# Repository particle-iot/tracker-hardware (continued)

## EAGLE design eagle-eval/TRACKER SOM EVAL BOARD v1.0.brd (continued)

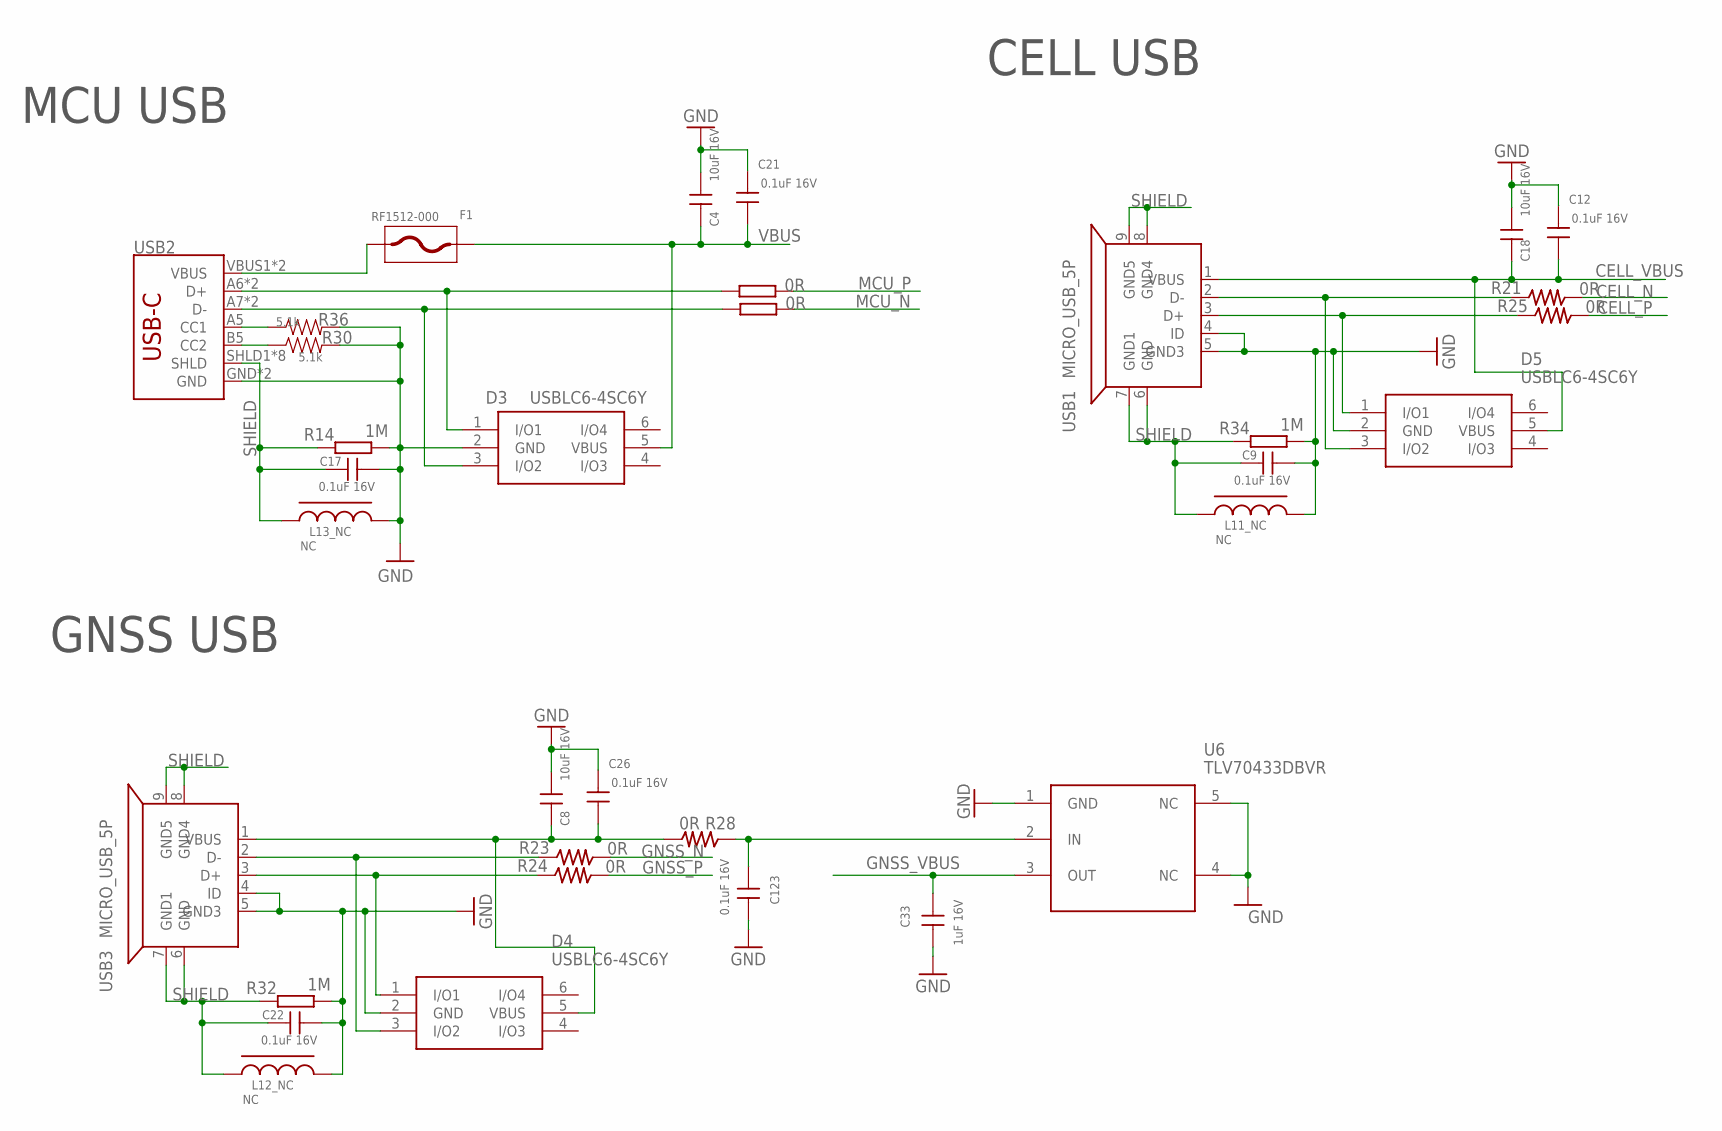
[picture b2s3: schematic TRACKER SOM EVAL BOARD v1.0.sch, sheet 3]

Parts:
C4, C8, C18: 10uF 16V; REDBEAR_C0603
C9, C17, C22: 0.1uF 16V; PARTICLE-SZ_C-0402
C12, C21, C26, C123: 0.1uF 16V; C-0402
C33: 1uF 16V; C0603
D3, D4, D5: USBLC6-4SC6Y; SOT95P280X145-6N
F1: RF1512-000; R1206
L11_NC, L12_NC, L13_NC: NC; R-0603A
R14, R32, R34: 1M; REDBEAR_R0603
R15, R16, R21, R23, R24, R25, R28: 0R; R-0402S
R30, R36: 5.1k; C0402
U6: TLV70433DBVR
USB1, USB3: MICRO_USB_5P; MICRO_USB
USB2: USB_C16PIN; USB-C-16P

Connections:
CELL_N: R21.2; also elsewhere on the board
CELL_P: R25.2; also elsewhere on the board
CELL_VBUS: C12.1, C18.2, D5.5 (VBUS), USB1.1 (VBUS); also elsewhere on the board
GND: C4.1, C8.1, C9.2, C12.2, C17.2, C18.1, C21.2, C22.2, C26.2, C33.2, C123.2, D3.2 (GND), D4.2 (GND), D5.2 (GND), L11_NC.2, L12_NC.2, L13_NC.2, R14.2, R30.2, R32.2, R34.2, R36.2, U6.1 (GND), U6.4 (NC), U6.5 (NC), USB1.4 (ID), USB1.5 (GND3), USB2.GND, USB2.GND2 (GND), USB3.4 (ID), USB3.5 (GND3); also elsewhere on the board
GNSS_N: R23.2; also elsewhere on the board
GNSS_P: R24.2; also elsewhere on the board
GNSS_VBUS: C33.1, U6.3 (OUT); also elsewhere on the board
MCU_N: R15.2; also elsewhere on the board
MCU_P: R16.2; also elsewhere on the board
unnamed: D3.3 (I/O2), R15.1, USB2.A7 (D-), USB2.B7 (D-)
unnamed: D3.1 (I/O1), R16.1, USB2.A6 (D+), USB2.B6 (D+)
unnamed: D4.3 (I/O2), R23.1, USB3.2 (D-)
unnamed: D5.3 (I/O2), R21.1, USB1.2 (D-)
unnamed: D5.1 (I/O1), R25.1, USB1.3 (D+)
unnamed: F1.1, USB2.VBUS1 (VBUS), USB2.VBUS2 (VBUS)
unnamed: D4.1 (I/O1), R24.1, USB3.3 (D+)
unnamed: C123.1, R28.1, U6.2 (IN)
unnamed: R30.1, USB2.B5 (CC2)
unnamed: R36.1, USB2.A5 (CC1)
SHIELD: C9.1, C17.1, C22.1, L11_NC.1, L12_NC.1, L13_NC.1, R14.1, R32.1, R34.1, USB1.6 (GND), USB1.7 (GND1), USB1.8 (GND4), USB1.9 (GND5), USB2.SHLD1 (SHLD), USB2.SHLD2 (SHLD), USB2.SHLD3 (SHLD), USB2.SHLD4 (SHLD), USB2.SHLD5 (SHLD), USB2.SHLD6 (SHLD), USB2.SHLD7 (SHLD), USB2.SHLD8 (SHLD), USB3.6 (GND), USB3.7 (GND1), USB3.8 (GND4), USB3.9 (GND5)
U_VBUS: C8.2, C26.1, D4.5 (VBUS), R28.2, USB3.1 (VBUS)
VBUS: C4.2, C21.1, D3.5 (VBUS), F1.2; also elsewhere on the board

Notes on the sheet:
MCU USB
CELL USB
GNSS USB

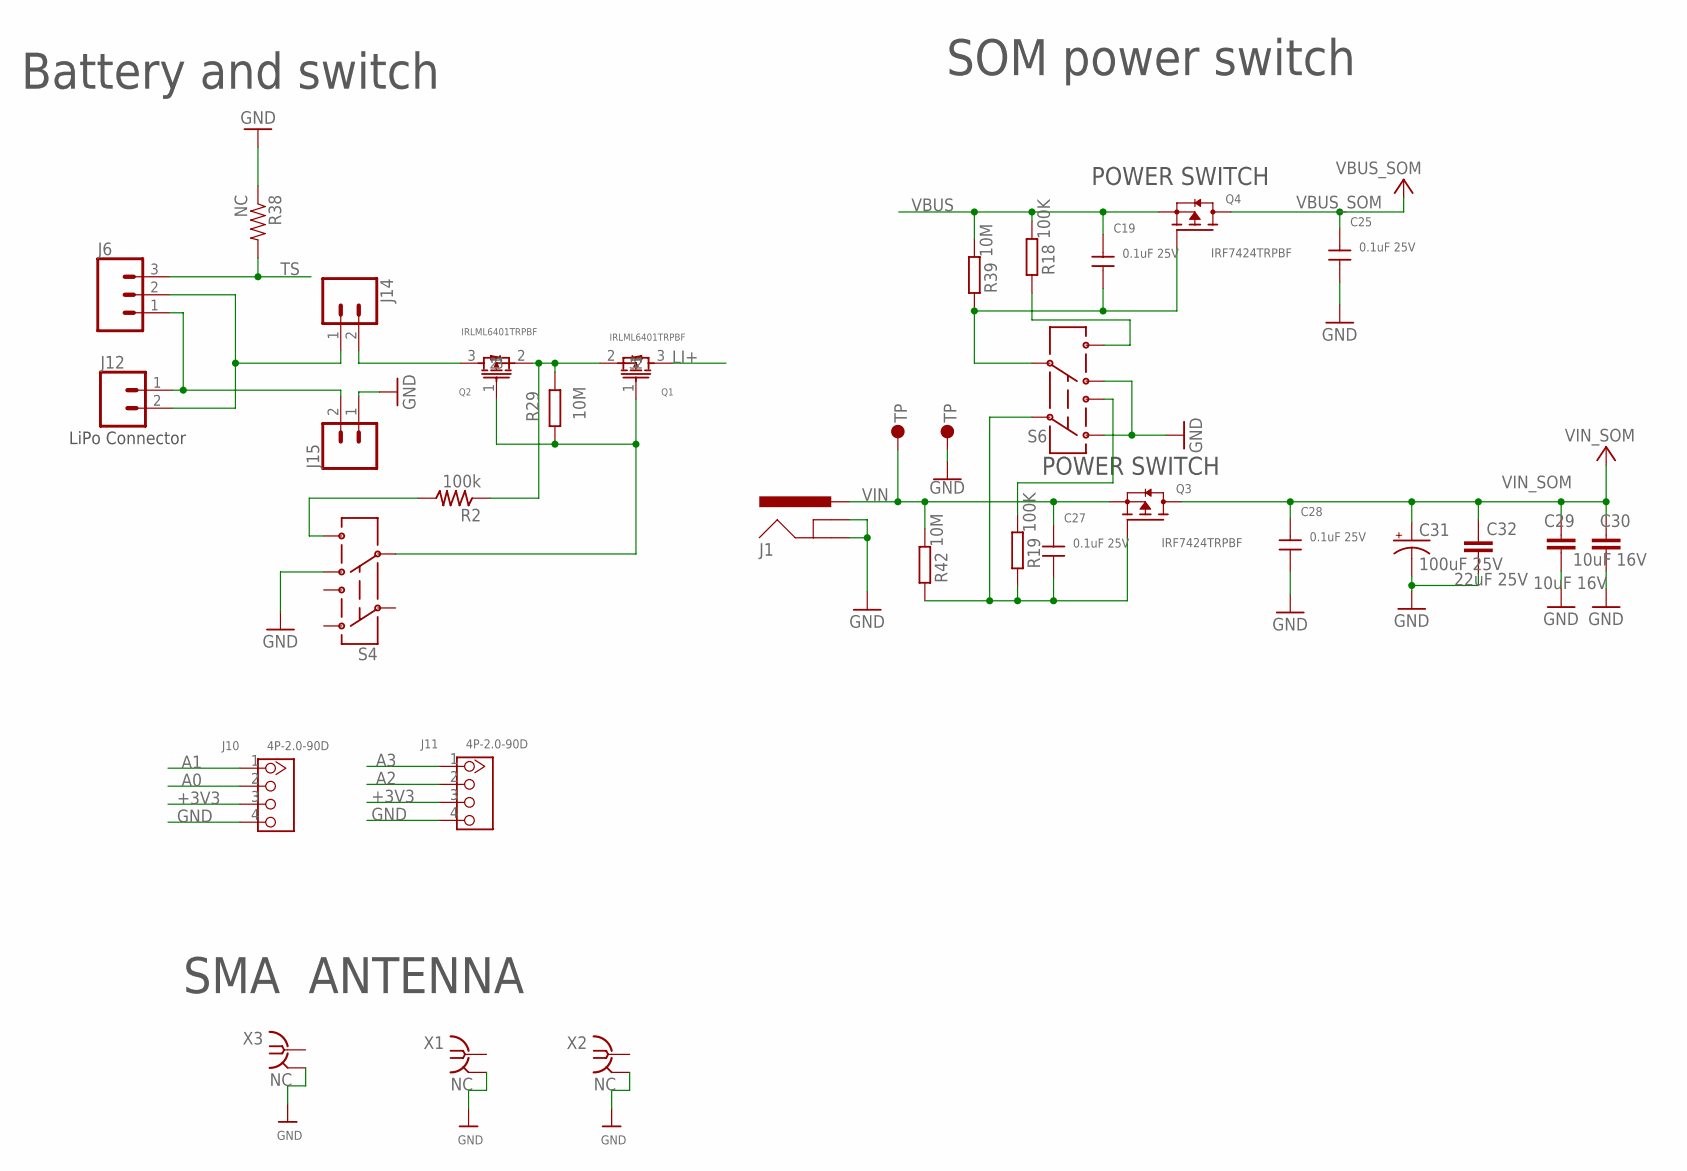
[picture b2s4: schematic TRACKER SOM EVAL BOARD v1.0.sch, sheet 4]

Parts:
C19, C25, C27, C28: 0.1uF 25V; C-0402
C29, C30: 10uF 16V; C0805
C31: 100uF 25V; PANASONIC_D
C32: 22uF 25V; C1206
J1: POWER_JACKSLT; POWER_JACK_SLOT
J6: CONN_03_2.54MM; 1X03
J10, J11: 4P-2.0-90D; HW4-2.0-90D
J12: CONN_02-JST-2MM-SMT; JST-2-SMD
J14, J15: CONN_02; 1X02
Q1, Q2: IRLML6401TRPBF; SOT-23
Q3, Q4: IRF7424TRPBF; PMOS_IRF7424
R2: 100k; R-0402S
R18, R19: 100K; R0603
R29, R39, R42: 10M; R0603
R38: NC; 0603-RES
S4, S6: SWITCH-DPDT; SWITCH-2.5X3.2-6
U$9, U$10: TP2; TP70_BOT
X1, X2, X3: NC; BU-SMA-G

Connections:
+3V3: J10.3, J11.3; also elsewhere on the board
A0: J10.2; also elsewhere on the board
A1: J10.1; also elsewhere on the board
A2: J11.2; also elsewhere on the board
A3: J11.1; also elsewhere on the board
GND: C25.1, C28.1, C29.2, C30.2, C31.-, C32.2, J1.GND@1 (GNDBREAK), J1.GND@2 (GND), J10.4, J11.4, J15.1, R38.1, S4.4, S6.1, S6.4, U$10.P$1, X1.2, X1.3 (2), X1.4 (2), X1.5 (2), X2.2, X2.3 (2), X2.4 (2), X2.5 (2), X3.2, X3.3 (2), X3.4 (2), X3.5 (2); also elsewhere on the board
LI+: Q1.3; also elsewhere on the board
unnamed: J14.2, Q2.3
unnamed: R2.2, S4.6
unnamed: J6.1, J12.1 (2), J15.2
unnamed: R18.1, S6.6
unnamed: R19.2, S6.3
unnamed: J6.2, J12.2 (1), J14.1
unnamed: Q1.2, Q2.2, R2.1, R29.2
unnamed: Q1.1, Q2.1, R29.1, S4.5
SYS_PWR_EN1: C19.1, Q4.4 (G), R39.1, S6.5
SYS_PWR_EN2: C27.1, Q3.4 (G), R19.1, R42.1, S6.2
TS: J6.3, R38.2; also elsewhere on the board
VBUS: C19.2, Q4.1 (S), Q4.2 (S), Q4.3 (S), R18.2, R39.2; also elsewhere on the board
VBUS_SOM: C25.2, Q4.5 (D), Q4.6 (D), Q4.7 (D), Q4.8 (D); also elsewhere on the board
VIN: C27.2, J1.PWR, Q3.1 (S), Q3.2 (S), Q3.3 (S), R42.2, U$9.P$1
VIN_SOM: C28.2, C29.1, C30.1, C31.+, C32.1, Q3.5 (D), Q3.6 (D), Q3.7 (D), Q3.8 (D); also elsewhere on the board

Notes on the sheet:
LiPo Connector
SMA ANTENNA
SOM power switch
Battery and switch
POWER SWITCH

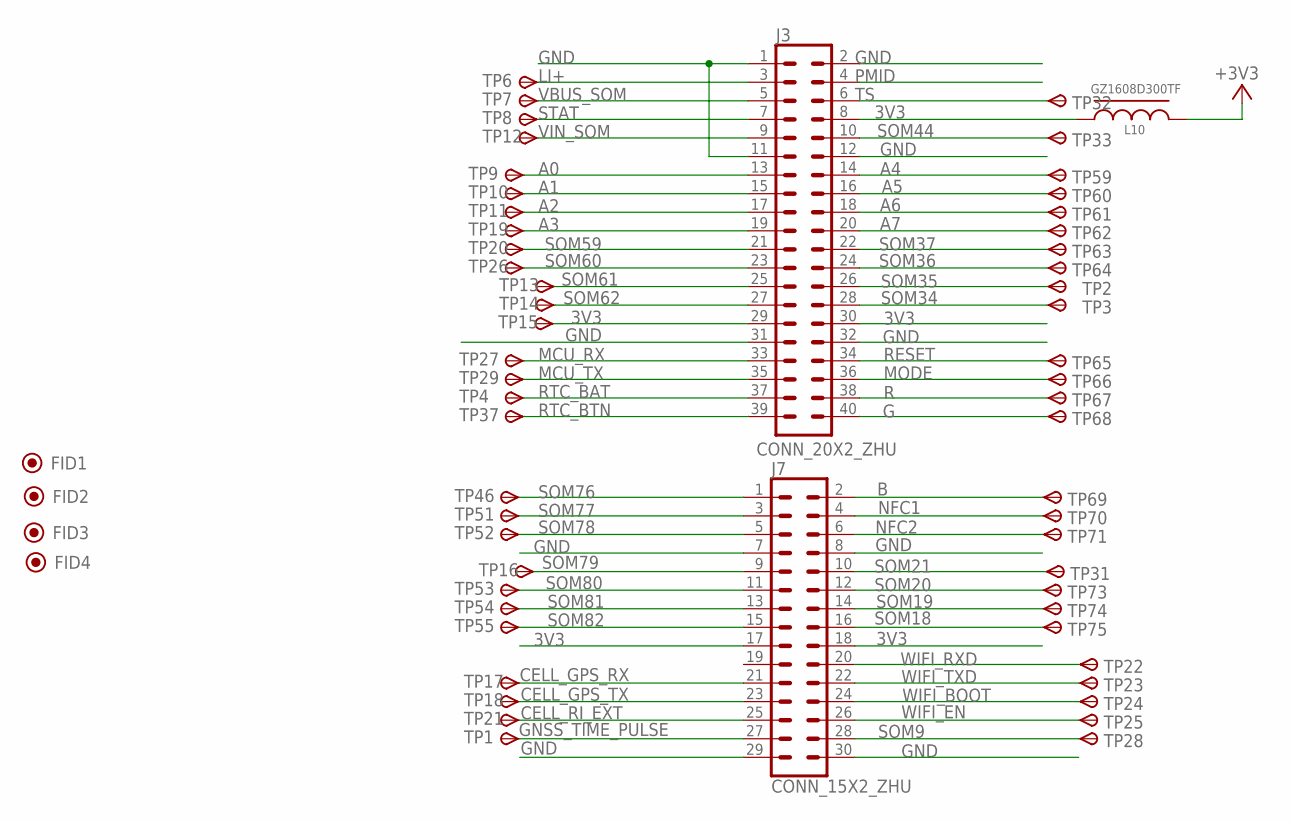
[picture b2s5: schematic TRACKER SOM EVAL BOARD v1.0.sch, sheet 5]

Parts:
FID1, FID2, FID3, FID4: FIDUCIAL_2; FID_TOP_1MM
J3: CONN_20X2_ZHU; SMD_2*20
J7: CONN_15X2_ZHU; SMD_2*15
L10: GZ1608D300TF; R-0603A
TP1, TP2, TP3, TP4, TP6, TP7, TP8, TP9, TP10, TP11, TP12, TP13, TP14, TP15, TP16, TP17, TP18, TP19, TP20, TP21, TP22, TP23, TP24, TP25, TP26, TP27, TP28, TP29, TP31, TP32, TP33, TP37, TP46, TP51, TP52, TP53, TP54, TP55, TP59, TP60, TP61, TP62, TP63, TP64, TP65, TP66, TP67, TP68, TP69, TP70, TP71, TP73, TP74, TP75: TPSB1,27; B1,27

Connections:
3V3: J3.8, J3.29, J3.30, J7.17, J7.18, L10.1, TP15.TP
+3V3: L10.2; also elsewhere on the board
A0: J3.13, TP9.TP; also elsewhere on the board
A1: J3.15, TP10.TP; also elsewhere on the board
A2: J3.17, TP11.TP; also elsewhere on the board
A3: J3.19, TP19.TP; also elsewhere on the board
A4: J3.14, TP59.TP; also elsewhere on the board
A5: J3.16, TP60.TP; also elsewhere on the board
A6: J3.18, TP61.TP; also elsewhere on the board
A7: J3.20, TP62.TP; also elsewhere on the board
B: J7.2, TP69.TP; also elsewhere on the board
CELL_GPS_RX: J7.21, TP17.TP; also elsewhere on the board
CELL_GPS_TX: J7.23, TP18.TP; also elsewhere on the board
CELL_RI_EXT: J7.25, TP21.TP; also elsewhere on the board
G: J3.40, TP68.TP; also elsewhere on the board
GND: J3.1, J3.2, J3.11, J3.12, J3.31, J3.32, J7.7, J7.8, J7.29, J7.30; also elsewhere on the board
GNSS_TIME_PULSE: J7.27, TP1.TP; also elsewhere on the board
LI+: J3.3, TP6.TP; also elsewhere on the board
MCU_RX: J3.33, TP27.TP; also elsewhere on the board
MCU_TX: J3.35, TP29.TP; also elsewhere on the board
MODE: J3.36, TP66.TP; also elsewhere on the board
NFC1: J7.4, TP70.TP; also elsewhere on the board
NFC2: J7.6, TP71.TP; also elsewhere on the board
PMID: J3.4; also elsewhere on the board
R: J3.38, TP67.TP; also elsewhere on the board
RESET: J3.34, TP65.TP; also elsewhere on the board
RTC_BAT: J3.37, TP4.TP; also elsewhere on the board
RTC_BTN: J3.39, TP37.TP; also elsewhere on the board
SOM9: J7.28, TP28.TP; also elsewhere on the board
SOM18: J7.16, TP75.TP; also elsewhere on the board
SOM19: J7.14, TP74.TP; also elsewhere on the board
SOM20: J7.12, TP73.TP; also elsewhere on the board
SOM21: J7.10, TP31.TP; also elsewhere on the board
SOM34: J3.28, TP3.TP; also elsewhere on the board
SOM35: J3.26, TP2.TP; also elsewhere on the board
SOM36: J3.24, TP64.TP; also elsewhere on the board
SOM37: J3.22, TP63.TP; also elsewhere on the board
SOM44: J3.10, TP33.TP; also elsewhere on the board
SOM59: J3.21, TP20.TP; also elsewhere on the board
SOM60: J3.23, TP26.TP; also elsewhere on the board
SOM61: J3.25, TP13.TP; also elsewhere on the board
SOM62: J3.27, TP14.TP; also elsewhere on the board
SOM76: J7.1, TP46.TP; also elsewhere on the board
SOM77: J7.3, TP51.TP; also elsewhere on the board
SOM78: J7.5, TP52.TP; also elsewhere on the board
SOM79: J7.9, TP16.TP; also elsewhere on the board
SOM80: J7.11, TP53.TP; also elsewhere on the board
SOM81: J7.13, TP54.TP; also elsewhere on the board
SOM82: J7.15, TP55.TP; also elsewhere on the board
STAT: J3.7, TP8.TP; also elsewhere on the board
TS: J3.6, TP32.TP; also elsewhere on the board
VBUS_SOM: J3.5, TP7.TP; also elsewhere on the board
VIN_SOM: J3.9, TP12.TP; also elsewhere on the board
WIFI_BOOT: J7.24, TP24.TP; also elsewhere on the board
WIFI_EN: J7.26, TP25.TP; also elsewhere on the board
WIFI_RXD: J7.20, TP22.TP; also elsewhere on the board
WIFI_TXD: J7.22, TP23.TP; also elsewhere on the board

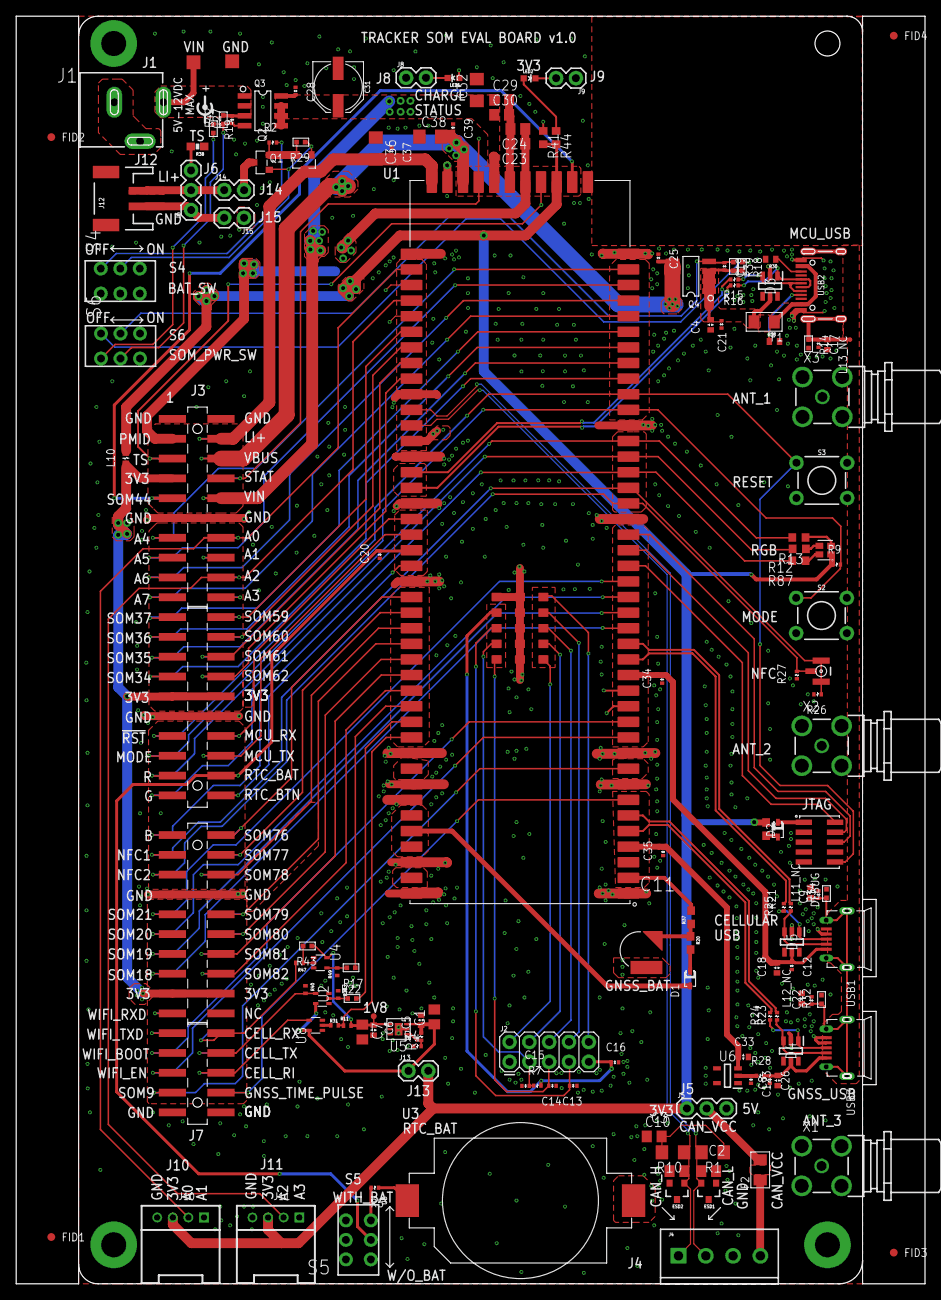
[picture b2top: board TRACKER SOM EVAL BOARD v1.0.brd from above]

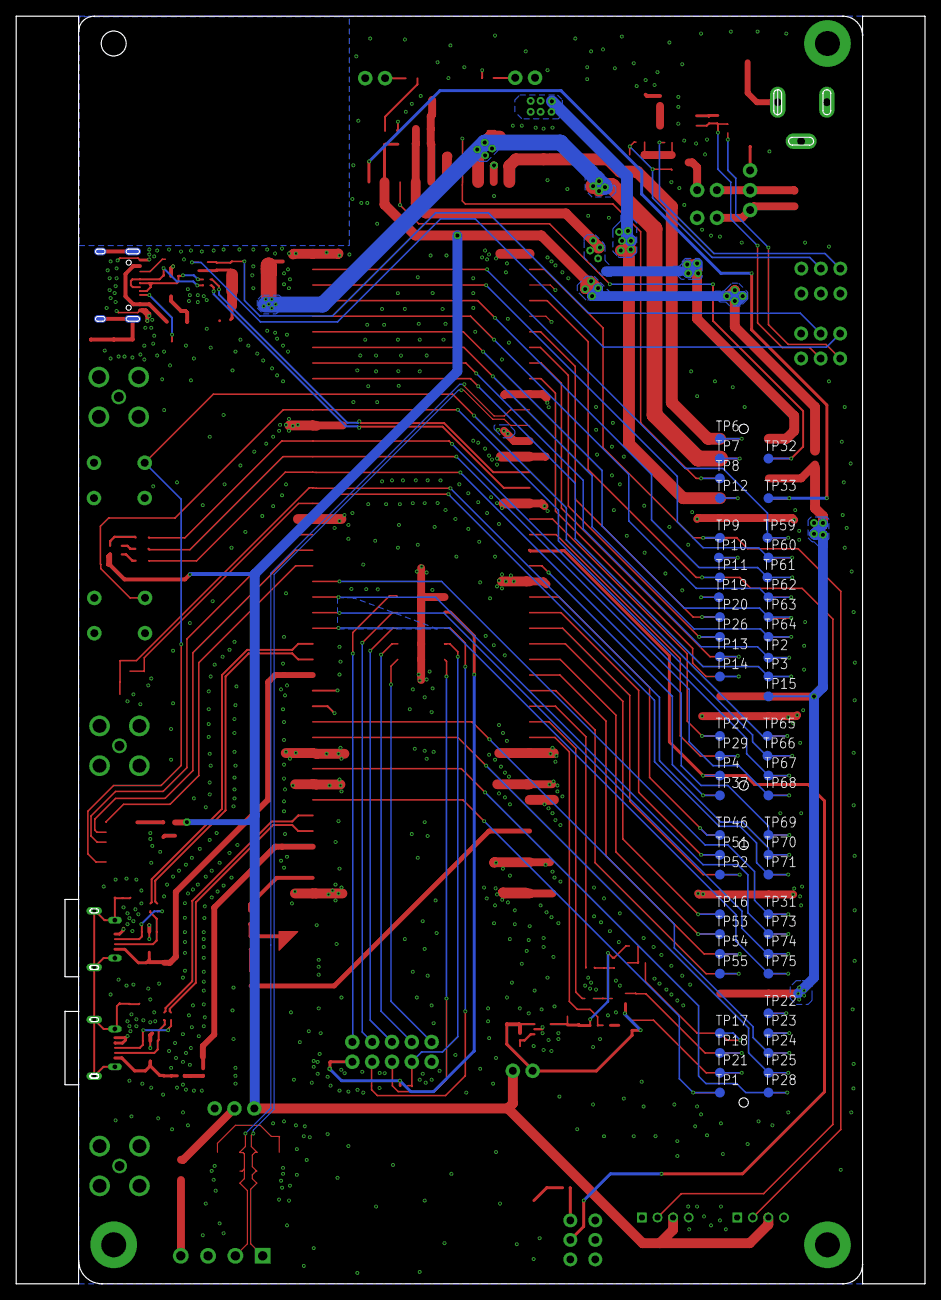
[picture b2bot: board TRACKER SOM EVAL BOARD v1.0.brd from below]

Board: 4 copper layers, 116.5 x 162.5 mm, 201 parts (56 on the bottom side), 132 nets.

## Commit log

2020-09-30 Add pdf schematics
2021-02-17 Update carrier board
